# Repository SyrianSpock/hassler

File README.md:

Portable Hassler circuit
========================

Portable version of the hassler circuit to get rid of office noise.

This project focuses on building a portable version of the Hassler circuit.
Inspired by the analog pioneer Bob Widlar and the work of Craig at [analog zoo](http://www.analogzoo.com/2015/01/building-the-widlar-hassler).

Features:
---------
* Emits a high frequency sound when there is noise
* Runs on one LiPo / Lithium-ion cell battery
* Micro USB rechargeable

License
-------
This project is released under the Creative Commons CC-BY-SA-4.0 license.
See http://creativecommons.org/licenses/by-sa/4.0/ for details.

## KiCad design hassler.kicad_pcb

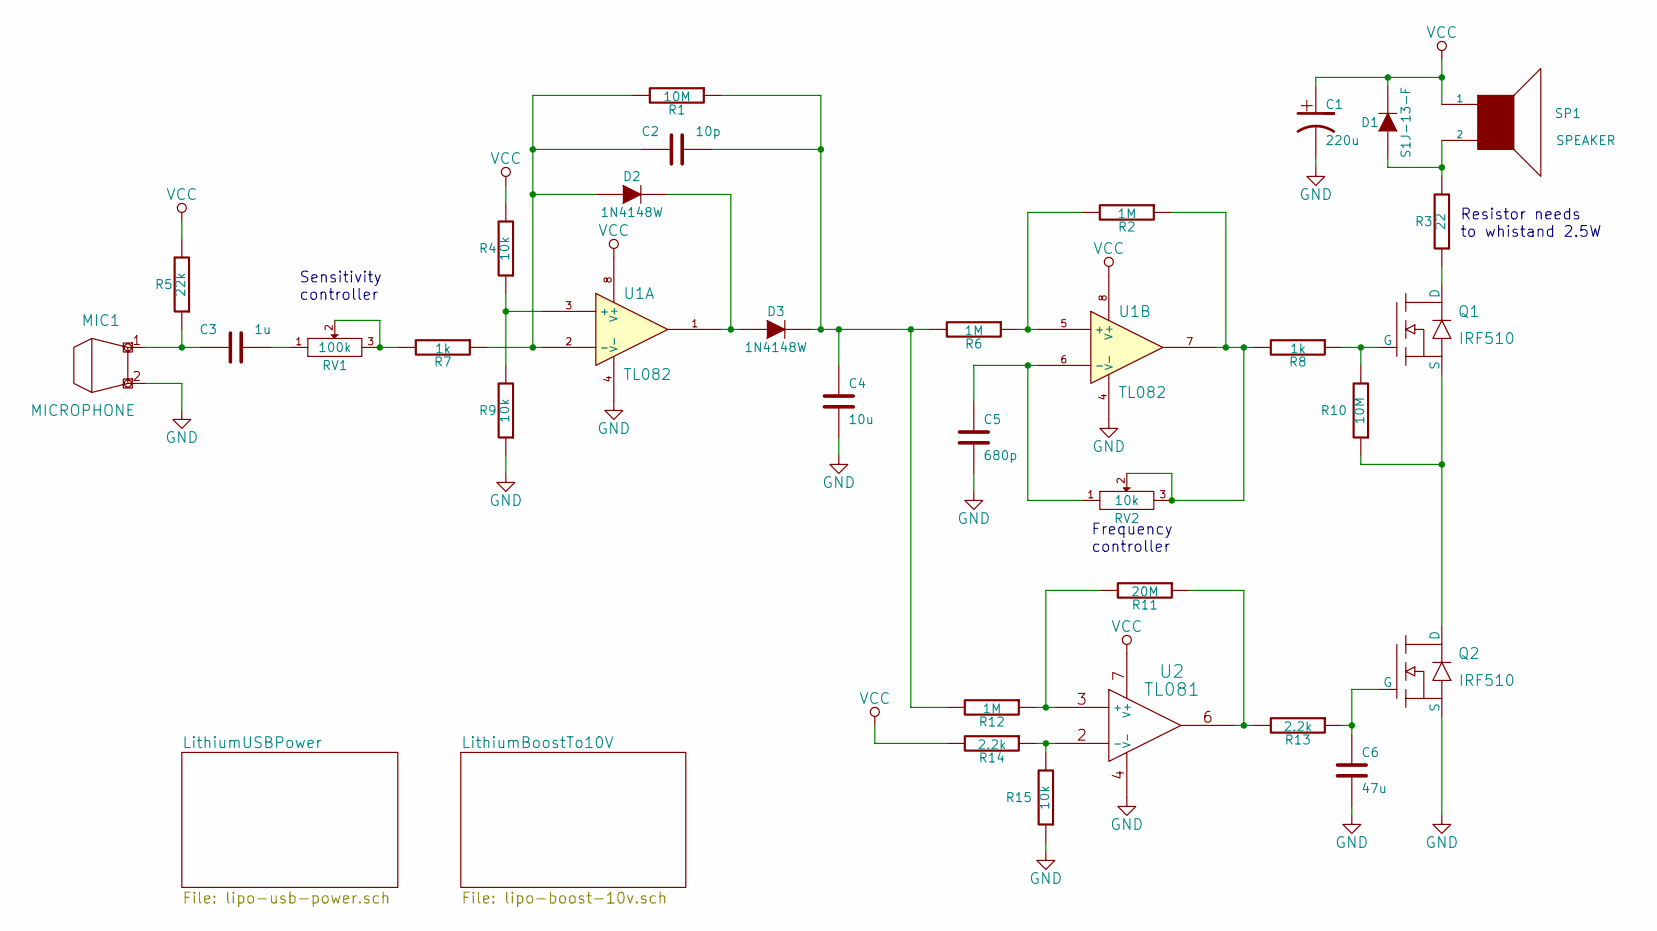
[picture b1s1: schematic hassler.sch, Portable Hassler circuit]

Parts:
C1: 220u
C2: 10p
C3: 1u
C4: 10u
C5: 680p
C6: 47u
D1: S1J-13-F
D2, D3: 1N4148W
MIC1: MICROPHONE
Q1, Q2: IRF510
R1, R10: 10M
R2, R6, R12: 1M
R3: 22
R4, R9, R15: 10k
R5: 22k
R7, R8: 1k
R11: 20M
R13, R14: 2.2k
RV1: 100k
RV2: 10k
SP1: SPEAKER
U1: TL082
U2: TL081

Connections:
GND: C1.2, C4.2, C5.2, C6.2, MIC1.2 (MIC-), Q2.3 (S), R9.1, R15.1, U1.4 (V-), U2.4 (V-); also elsewhere on the board
unnamed: C2.1, C4.1, D3.2 (K), R1.1, R6.2, R12.2
unnamed: C2.2, D2.1 (A), R1.2, R7.1, U1.2 (-)
unnamed: C3.1, MIC1.1 (MIC+), R5.1
unnamed: C3.2, RV1.1
unnamed: C5.1, RV2.1, U1.6 (-)
unnamed: C6.1, Q2.1 (G), R13.1
unnamed: D1.1 (A), R3.2, SP1.2
unnamed: D2.2 (K), D3.1 (A), U1.1
unnamed: Q1.1 (G), R8.1, R10.2
unnamed: Q1.2 (D), R3.1
unnamed: Q1.3 (S), Q2.2 (D), R10.1
unnamed: R2.1, R8.2, RV2.2, RV2.3, U1.7
unnamed: R2.2, R6.1, U1.5 (+)
unnamed: R4.1, R9.2, U1.3 (+)
unnamed: R7.2, RV1.2, RV1.3
unnamed: R11.1, R13.2, U2.6
unnamed: R11.2, R12.1, U2.3 (+)
unnamed: R14.1, R15.2, U2.2 (-)
VCC: C1.1, D1.2 (K), R4.2, R5.2, R14.2, SP1.1, U1.8 (V+), U2.7 (V+); also elsewhere on the board

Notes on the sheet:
Resistor needs to whistand 2.5W
Frequency controller
Sensitivity controller

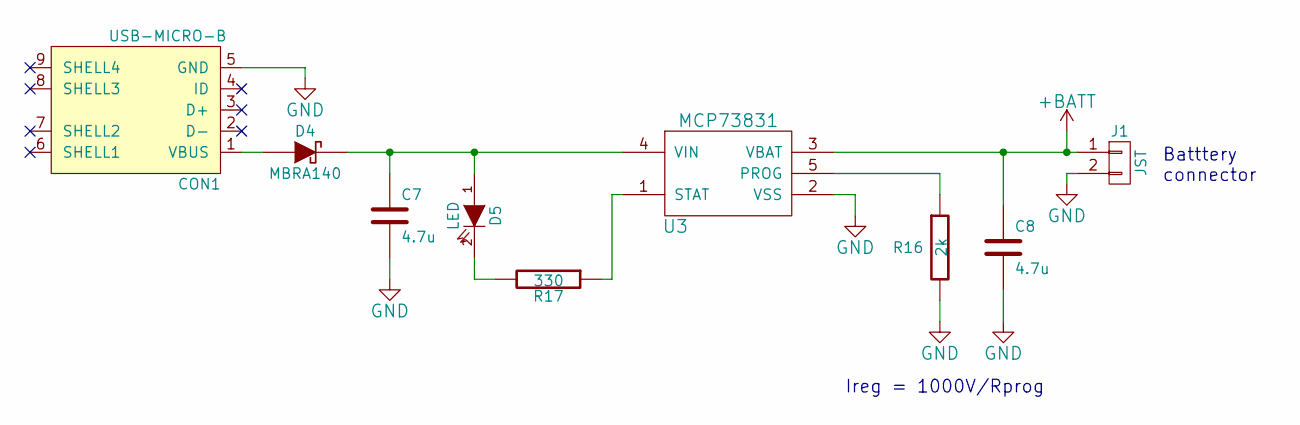
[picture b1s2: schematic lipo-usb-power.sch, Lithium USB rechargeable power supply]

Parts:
C7, C8: 4.7u
CON1: USB-MICRO-B
D4: MBRA140
D5: LED
J1: JST
R16: 2k
R17: 330
U3: MCP73831

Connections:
+BATT: C8.1, J1.1, U3.3 (VBAT); also elsewhere on the board
GND: C7.2, C8.2, CON1.5 (GND), J1.2, R16.2, U3.2 (VSS); also elsewhere on the board
unnamed: C7.1, D4.2 (K), D5.1 (A), U3.4 (VIN)
unnamed: CON1.1 (VBUS), D4.1 (A)
unnamed: D5.2 (K), R17.2
unnamed: R16.1, U3.5 (PROG)
unnamed: R17.1, U3.1 (STAT)

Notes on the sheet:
Ireg = 1000V/Rprog
Batttery connector

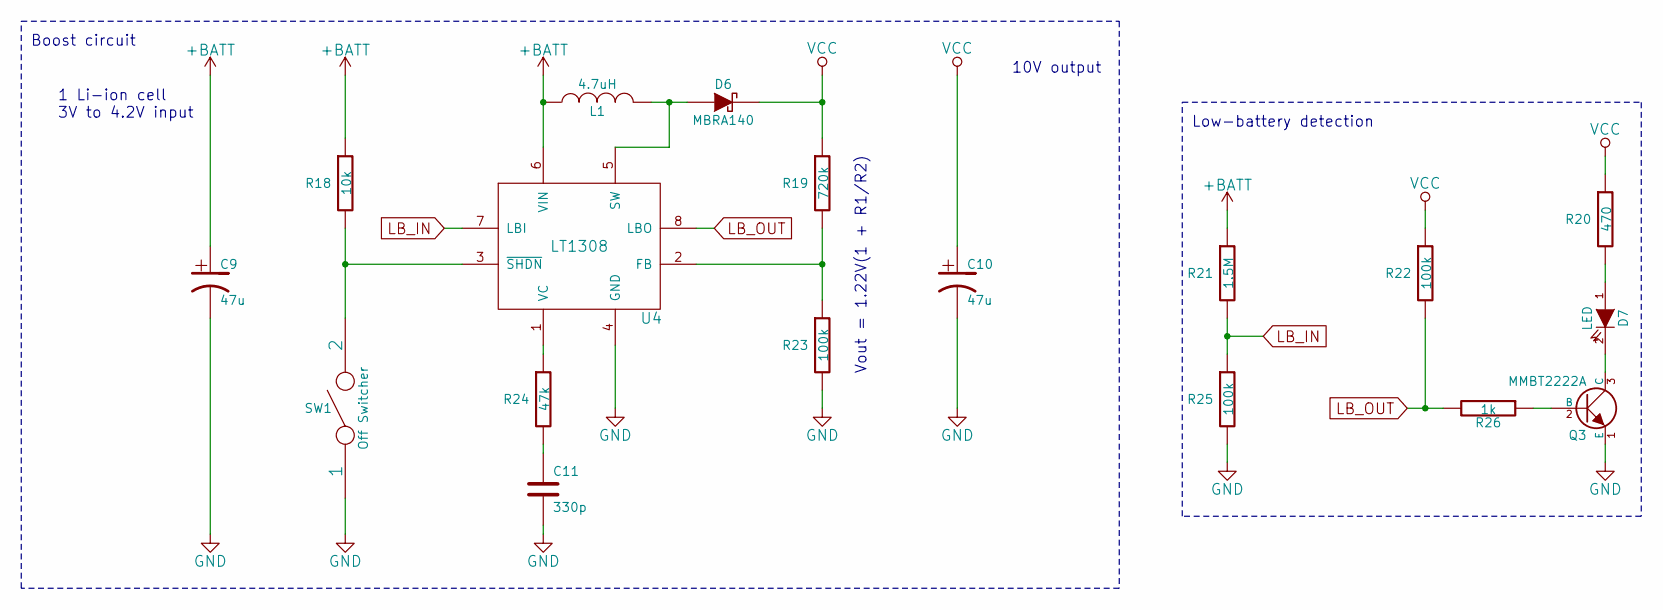
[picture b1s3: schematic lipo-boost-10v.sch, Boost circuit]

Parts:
C9, C10: 47u
C11: 330p
D6: MBRA140
D7: LED
L1: 4.7uH
Q3: MMBT2222A
R18: 10k
R19: 720k
R20: 470
R21: 1.5M
R22, R23, R25: 100k
R24: 47k
R26: 1k
SW1: Off Switcher
U4: LT1308

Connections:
+BATT: C9.1, L1.1, R18.1, R21.1, U4.6 (VIN); also elsewhere on the board
GND: C9.2, C10.2, C11.2, Q3.1 (E), R23.2, R25.2, SW1.1, U4.4 (GND); also elsewhere on the board
LB_IN: R21.2, R25.1, U4.7 (LBI)
LB_OUT: R22.2, R26.2, U4.8 (LBO)
unnamed: C11.1, R24.2
unnamed: D6.1 (A), L1.2, U4.5 (SW)
unnamed: D7.1 (A), R20.2
unnamed: D7.2 (K), Q3.3 (C)
unnamed: Q3.2 (B), R26.1
unnamed: R18.2, SW1.2, U4.3 (~SHDN)
unnamed: R19.2, R23.1, U4.2 (FB)
unnamed: R24.1, U4.1 (VC)
VCC: C10.1, D6.2 (K), R19.1, R20.1, R22.1; also elsewhere on the board

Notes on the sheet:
Vout = 1.22V(1 + R1/R2)
1 Li-ion cell 3V to 4.2V input
10V output
Low-battery detection
Boost circuit

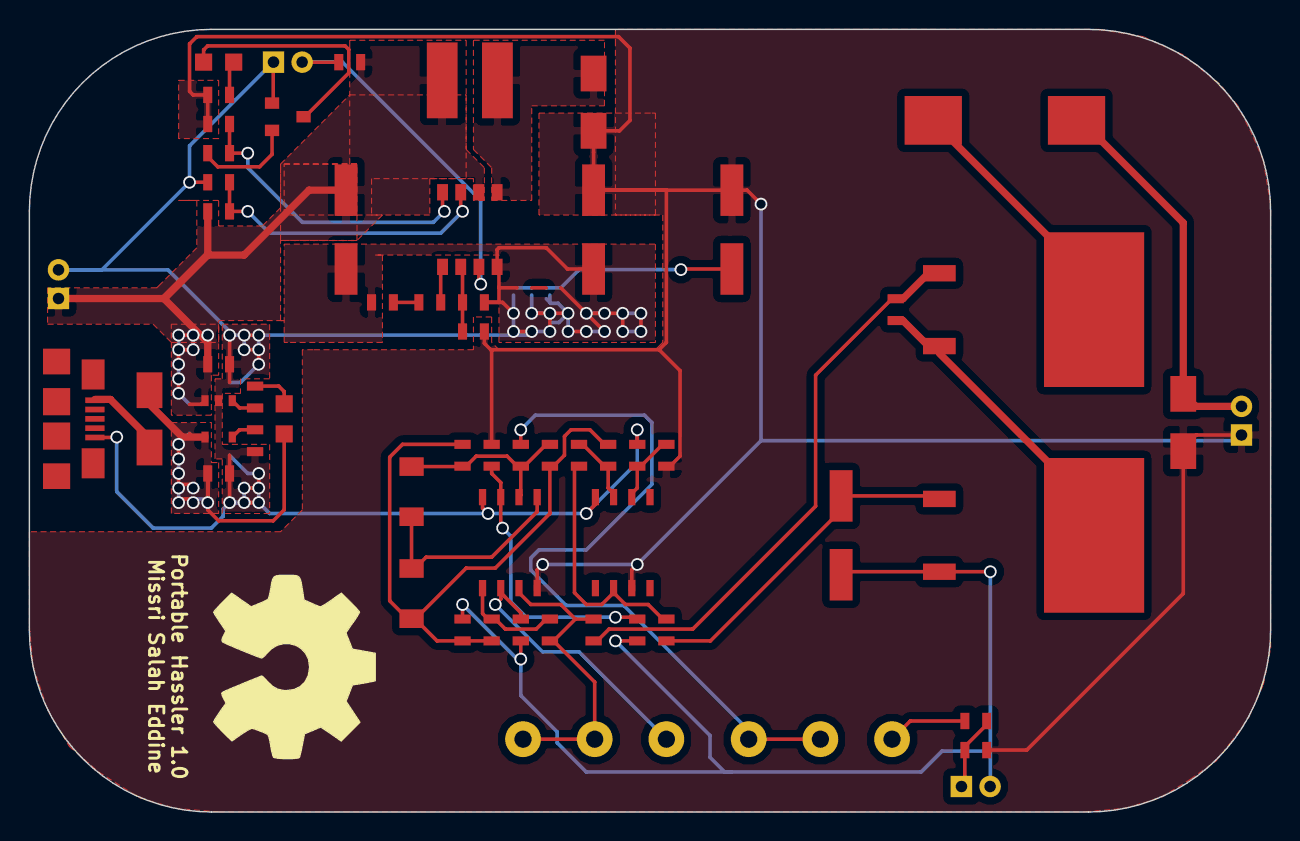
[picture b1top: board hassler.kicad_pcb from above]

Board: 2 copper layers, 86.6 x 54.6 mm, 59 parts (0 on the bottom side), 36 nets.

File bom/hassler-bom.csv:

Reference,Value,Quantity,Kicad Footprint,URL
C1,220u,1,Capacitors_SMD:c_elec_6.3x7.7,
C2,10p,1,SMD_Packages:SMD-0603,
C3,1u,1,SMD_Packages:SMD-0603,
C4,10u,1,SMD_Packages:SMD-0603,
C5,680p,1,SMD_Packages:SMD-0603,
C6 C9 C10,47u,3,Capacitors_SMD:c_elec_6.3x7.7,
C7 C8,4.7u,2,SMD_Packages:SMD-0603,
C11,330p,1,SMD_Packages:SMD-0603,
CON1,USB-MICRO-B,1,_connectors:_Micro-USB-AB-receptacle-SMT,
D1,S1J-13-F,1,Diodes_SMD:Diode-SMA_Standard,
D2 D3,1N4148W,2,Diodes_SMD:Diode-MiniMELF_Standard,
D4 D6,MBRA140,2,Diodes_SMD:Diode-SMA_Standard,
D5 D7,LED,2,LEDs:LED-0805,
J1,JST,1,_connectors:_Pin2mm_2,
L1,4.7uH,1,_standard:Inductor2300,
MIC1,MICROPHONE,1,_connectors:_Pin2mm_2,
Q1 Q2,IRF510,2,_standard:TO-263,
Q3,MMBT2222A,1,SMD_Packages:SOT-23,
R1 R10,10M,2,SMD_Packages:SMD-0603,
R2 R6 R12,1M,3,SMD_Packages:SMD-0603,
R3,22,1,_standard:PowerRes_SM_3,
R4 R9 R15 R18,10k,4,SMD_Packages:SMD-0603,
R5,22k,1,SMD_Packages:SMD-0603,
R7 R8 R26,1k,3,SMD_Packages:SMD-0603,
R11,20M,1,SMD_Packages:SMD-0603,
R13 R14,2.2k,2,SMD_Packages:SMD-0603,
R16,2k,1,SMD_Packages:SMD-0603,
R17,330,1,SMD_Packages:SMD-0603,
R19,720k,1,SMD_Packages:SMD-0603,
R20,470,1,SMD_Packages:SMD-0603,
R21,1.5M,1,SMD_Packages:SMD-0603,
R22 R23 R25,100k,3,SMD_Packages:SMD-0603,
R24,47k,1,SMD_Packages:SMD-0603,
RV1,100k,1,Potentiometers:Potentiometer_WirePads_largePads,
RV2,10k,1,Potentiometers:Potentiometer_WirePads_largePads,
SP1,SPEAKER,1,_connectors:_Pin2mm_2,
SW1,Off Switcher,1,_connectors:_Pin2mm_2,
U1,TL082,1,SMD_Packages:SOIC-8-N,
U2,TL081,1,SMD_Packages:SOIC-8-N,
U3,MCP73831,1,SMD_Packages:SOT-23-5,
U4,LT1308,1,_standard:S8,

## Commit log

2015-02-02 Add library as submodule
2015-02-02 Add hassler circuit
2015-02-02 Add power supply circuit with Lithium battery and USB recharge
2015-02-02 Add datasheets of main components
2015-02-03 Minor corrections to schematic
2015-02-04 Add lithium cell to 10v boost circuit
2015-02-04 Add low-battery detection stage
2015-02-04 Correct value of a resistor & Generate netlist
2015-02-04 Associate footprints to components
2015-02-05 Finish footprint association & Add components to pcb
2015-02-05 Layout lipo recharge circuit
2015-02-06 Layout boost circuit
2015-02-06 Finish PCB layout
2015-02-06 Generate gerber files & Add bom
2015-02-10 Add license and OSH logo
